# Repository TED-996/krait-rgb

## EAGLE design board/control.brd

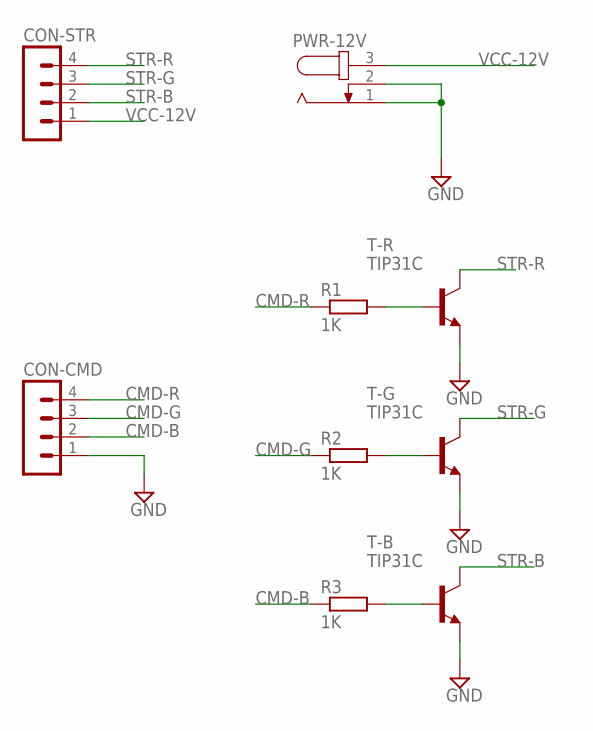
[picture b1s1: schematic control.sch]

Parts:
CON-CMD: MA04-1
CON-STR: MA04-1
PWR-12V: JACK-PLUG0; SPC4077
R1, R2, R3: 1K; 0207/10
T-B: TIP31C; TO220
T-G: TIP31C; TO220
T-R: TIP31C; TO220

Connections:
CMD-B: CON-CMD.2, R3.1
CMD-G: CON-CMD.3, R2.1
CMD-R: CON-CMD.4, R1.1
GND: CON-CMD.1, PWR-12V.1, PWR-12V.2, T-B.3 (E), T-G.3 (E), T-R.3 (E)
unnamed: R1.2, T-R.1 (B)
unnamed: R2.2, T-G.1 (B)
unnamed: R3.2, T-B.1 (B)
STR-B: CON-STR.2, T-B.2 (C)
STR-G: CON-STR.3, T-G.2 (C)
STR-R: CON-STR.4, T-R.2 (C)
VCC-12V: CON-STR.1, PWR-12V.3

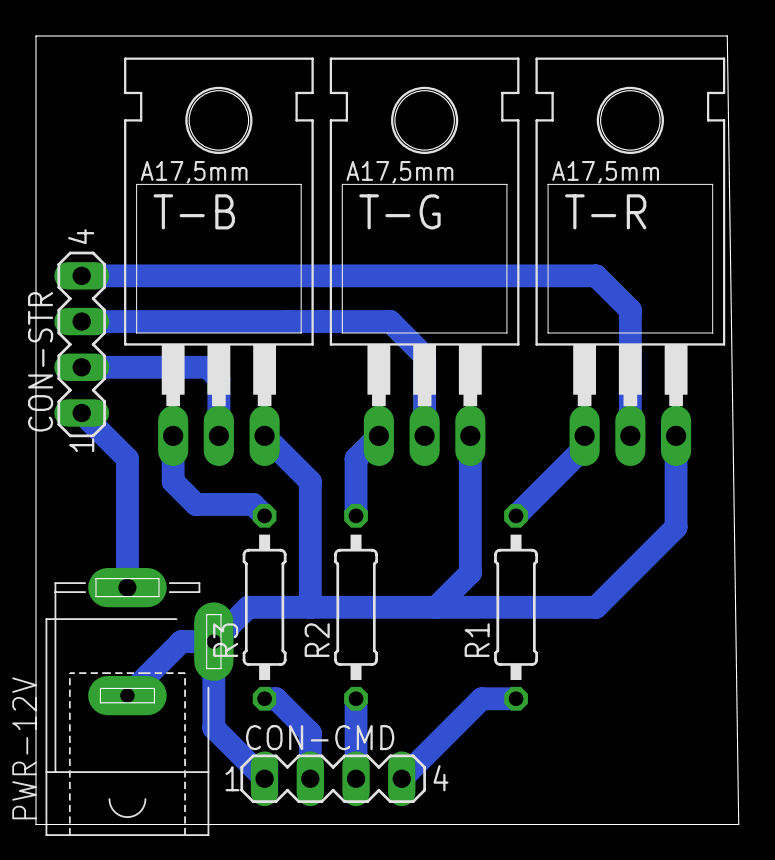
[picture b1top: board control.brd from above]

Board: 2 copper layers, 39.0 x 43.8 mm, 9 parts (0 on the bottom side), 11 nets.

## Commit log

2018-06-24 Added board
2018-06-24 Added LICENSE
2018-06-29 Removed old libs
